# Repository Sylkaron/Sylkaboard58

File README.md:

# Sylkaboard58

A split ortholinear keyboard with 58 keys and two encoders for a first step in my ergonomic journey

## Table des matières
- [Overview](#-overview)
- [BOM](#️-bill-of-materials)
- [Assemblage](#-assemblage)
- [Firmware](#-firmware)
- [Layout](#-keyboard-layout)
- [Licence](#-licence)

## Overview

## BOM
 ### Keyboard

 ### Tools

## Firmware
Powered by QMK

### Requirements
- [QMK Toolbox](https://github.com/qmk/qmk_toolbox) (to flash firmware).
- [QMK Firmware](https://github.com/qmk/qmk_firmware)

### Étapes pour flasher le firmware
1. Téléchargez ou clonez le dépôt QMK :
   ```bash
   git clone https://github.com/qmk/qmk_firmware.git

## Layout

## Licence  
This project is under **[CERN OHL v2](https://ohwr.org/cern_ohl)** 
This documentation is under **[CC BY-SA 4.0](https://creativecommons.org/licenses/by-sa/4.0/)**.

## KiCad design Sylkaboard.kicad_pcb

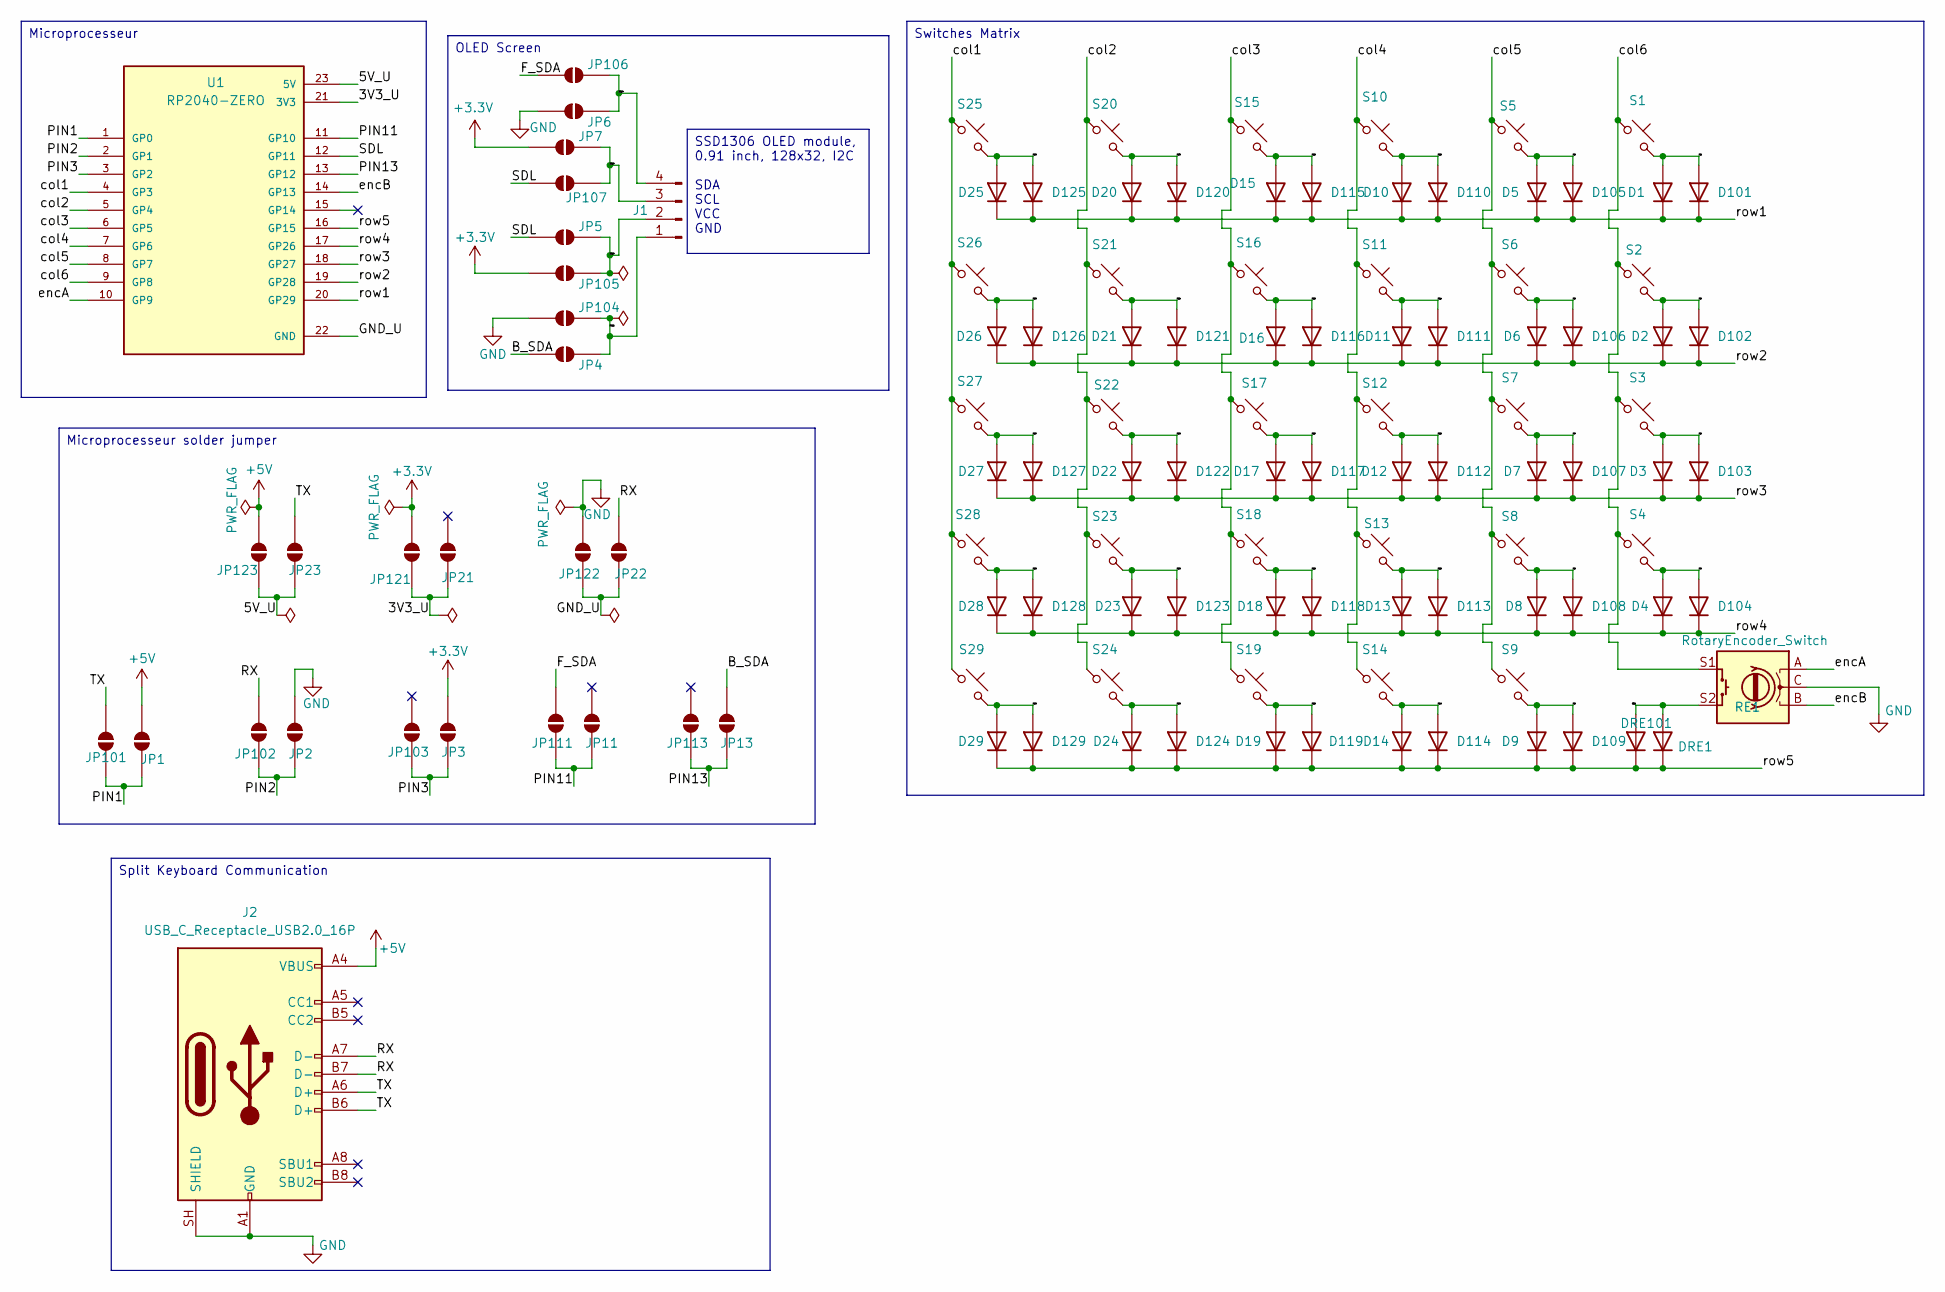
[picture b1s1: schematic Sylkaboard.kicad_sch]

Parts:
D1, D2, D3, D4, D5, D6, D7, D8, D9, D10, D11, D12, D13, D14, D15, D16, D17, D18, D19, D20, D21, D22, D23, D24, D25, D26, D27, D28, D29, D101, D102, D103, D104, D105, D106, D107, D108, D109, D110, D111, D112, D113, D114, D115, D116, D117, D118, D119, D120, D121, D122, D123, D124, D125, D126, D127, D128, D129: 1N4148W; D_SOD-123
DRE1, DRE101: 1N4148W; D_SOD-123
J1: Conn_01x04_Pin; PinHeader_1x04_P2.54mm_Vertical
J2: USB_C_Receptacle_USB2.0_16P; USB_C_Receptacle_G-Switch_GT-USB-7010ASV_REVERSIBLE
JP1, JP2, JP3, JP4, JP5, JP6, JP7, JP11, JP13, JP21, JP22, JP23, JP101, JP102, JP103, JP104, JP105, JP106, JP107, JP111, JP113, JP121, JP122, JP123: SolderJumper_2_Open; SolderJumper-2_P1.3mm_Open_TrianglePad1.0x1.5mm
RE1: RotaryEncoder_Switch; RotaryEncoder_Alps_EC11E-Switch_Vertical_H20mm
S1, S2, S3, S4, S5, S6, S7, S8, S9, S10, S11, S12, S13, S14, S15, S16, S17, S18, S19, S20, S21, S22, S23, S24, S25, S26, S27, S28, S29: SW_Push_45deg; Kail_Hotswap_Reversible_V1V2
U1: RP2040-ZERO; MODULE_RP2040-ZERO; PARTREV NA

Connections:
+3.3V: JP3.2 (B), JP7.2 (B), JP105.2 (B), JP121.2 (B)
+5V: J2.A4 (VBUS), J2.A9 (VBUS), J2.B4 (VBUS), J2.B9 (VBUS), JP1.2 (B), JP123.2 (B)
/3V3_U: JP21.1 (A_1), JP121.1 (A), U1.21 (3V3)
/5V_U: JP23.1 (A), JP123.1 (A), U1.23 (5V)
/B_SDA: JP4.2 (B), JP13.2 (B)
/F_SDA: JP106.2 (B), JP111.2 (B)
/GND_U: JP22.1 (A), JP122.1 (A), U1.22 (GND)
/OLED1: J1.1, JP4.1 (A), JP104.1 (A)
/OLED2: J1.2, JP5.1 (A), JP105.1 (A)
/OLED3: J1.3, JP7.1 (A), JP107.1 (A)
/OLED4: J1.4, JP6.1 (A), JP106.1 (A)
/PIN1: JP1.1 (A), JP101.1 (A), U1.1 (GP0)
/PIN2: JP2.1 (A), JP102.1 (A), U1.2 (GP1)
/PIN3: JP3.1 (A), JP103.1 (A_1), U1.3 (GP2)
/PIN11: JP11.1 (A_1), JP111.1 (A), U1.11 (GP10)
/PIN13: JP13.1 (A), JP113.1 (A_1), U1.13 (GP12)
/RED1: DRE1.2 (A), DRE101.2 (A), RE1.S2
/RX: J2.A7 (D-), J2.B7 (D-), JP22.2 (B), JP102.2 (B)
/SD1: D1.2 (A), D101.2 (A), S1.2
/SD2: D2.2 (A), D102.2 (A), S2.2
/SD3: D3.2 (A), D103.2 (A), S3.2
/SD4: D4.2 (A), D104.2 (A), S4.2
/SD5: D5.2 (A), D105.2 (A), S5.2
/SD6: D6.2 (A), D106.2 (A), S6.2
/SD7: D7.2 (A), D107.2 (A), S7.2
/SD8: D8.2 (A), D108.2 (A), S8.2
/SD9: D9.2 (A), D109.2 (A), S9.2
/SD10: D10.2 (A), D110.2 (A), S10.2
/SD11: D11.2 (A), D111.2 (A), S11.2
/SD12: D12.2 (A), D112.2 (A), S12.2
/SD13: D13.2 (A), D113.2 (A), S13.2
/SD14: D14.2 (A), D114.2 (A), S14.2
/SD15: D15.2 (A), D115.2 (A), S15.2
/SD16: D16.2 (A), D116.2 (A), S16.2
/SD17: D17.2 (A), D117.2 (A), S17.2
/SD18: D18.2 (A), D118.2 (A), S18.2
/SD19: D19.2 (A), D119.2 (A), S19.2
/SD20: D20.2 (A), D120.2 (A), S20.2
/SD21: D21.2 (A), D121.2 (A), S21.2
/SD22: D22.2 (A), D122.2 (A), S22.2
/SD23: D23.2 (A), D123.2 (A), S23.2
/SD24: D24.2 (A), D124.2 (A), S24.2
/SD25: D25.2 (A), D125.2 (A), S25.2
/SD26: D26.2 (A), D126.2 (A), S26.2
/SD27: D27.2 (A), D127.2 (A), S27.2
/SD28: D28.2 (A), D128.2 (A), S28.2
/SD29: D29.2 (A), D129.2 (A), S29.2
/SDL: JP5.2 (B), JP107.2 (B), U1.12 (GP11)
/TX: J2.A6 (D+), J2.B6 (D+), JP23.2 (B), JP101.2 (B)
/col1: S25.1, S26.1, S27.1, S28.1, S29.1, U1.4 (GP3)
/col2: S20.1, S21.1, S22.1, S23.1, S24.1, U1.5 (GP4)
/col3: S15.1, S16.1, S17.1, S18.1, S19.1, U1.6 (GP5)
/col4: S10.1, S11.1, S12.1, S13.1, S14.1, U1.7 (GP6)
/col5: S5.1, S6.1, S7.1, S8.1, S9.1, U1.8 (GP7)
/col6: RE1.S1, S1.1, S2.1, S3.1, S4.1, U1.9 (GP8)
/encA: RE1.A, U1.10 (GP9)
/encB: RE1.B, U1.14 (GP13)
/row1: D1.1 (K), D5.1 (K), D10.1 (K), D15.1 (K), D20.1 (K), D25.1 (K), D101.1 (K), D105.1 (K), D110.1 (K), D115.1 (K), D120.1 (K), D125.1 (K), U1.20 (GP29)
/row2: D2.1 (K), D6.1 (K), D11.1 (K), D16.1 (K), D21.1 (K), D26.1 (K), D102.1 (K), D106.1 (K), D111.1 (K), D116.1 (K), D121.1 (K), D126.1 (K), U1.19 (GP28)
/row3: D3.1 (K), D7.1 (K), D12.1 (K), D17.1 (K), D22.1 (K), D27.1 (K), D103.1 (K), D107.1 (K), D112.1 (K), D117.1 (K), D122.1 (K), D127.1 (K), U1.18 (GP27)
/row4: D4.1 (K), D8.1 (K), D13.1 (K), D18.1 (K), D23.1 (K), D28.1 (K), D104.1 (K), D108.1 (K), D113.1 (K), D118.1 (K), D123.1 (K), D128.1 (K), U1.17 (GP26)
/row5: D9.1 (K), D14.1 (K), D19.1 (K), D24.1 (K), D29.1 (K), D109.1 (K), D114.1 (K), D119.1 (K), D124.1 (K), D129.1 (K), DRE1.1 (K), DRE101.1 (K), U1.16 (GP15)
GND: J2.A1 (GND), J2.A12 (GND), J2.B1 (GND), J2.B12 (GND), J2.SH (SHIELD), JP2.2 (B), JP6.2 (B), JP104.2 (B), JP122.2 (B), RE1.C

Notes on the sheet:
Split Keyboard Communication
Microprocesseur solder jumper
Microprocesseur
SSD1306 OLED module, 0.91 inch, 128x32, I2C SDA SCL VCC GND
OLED Screen
Switches Matrix

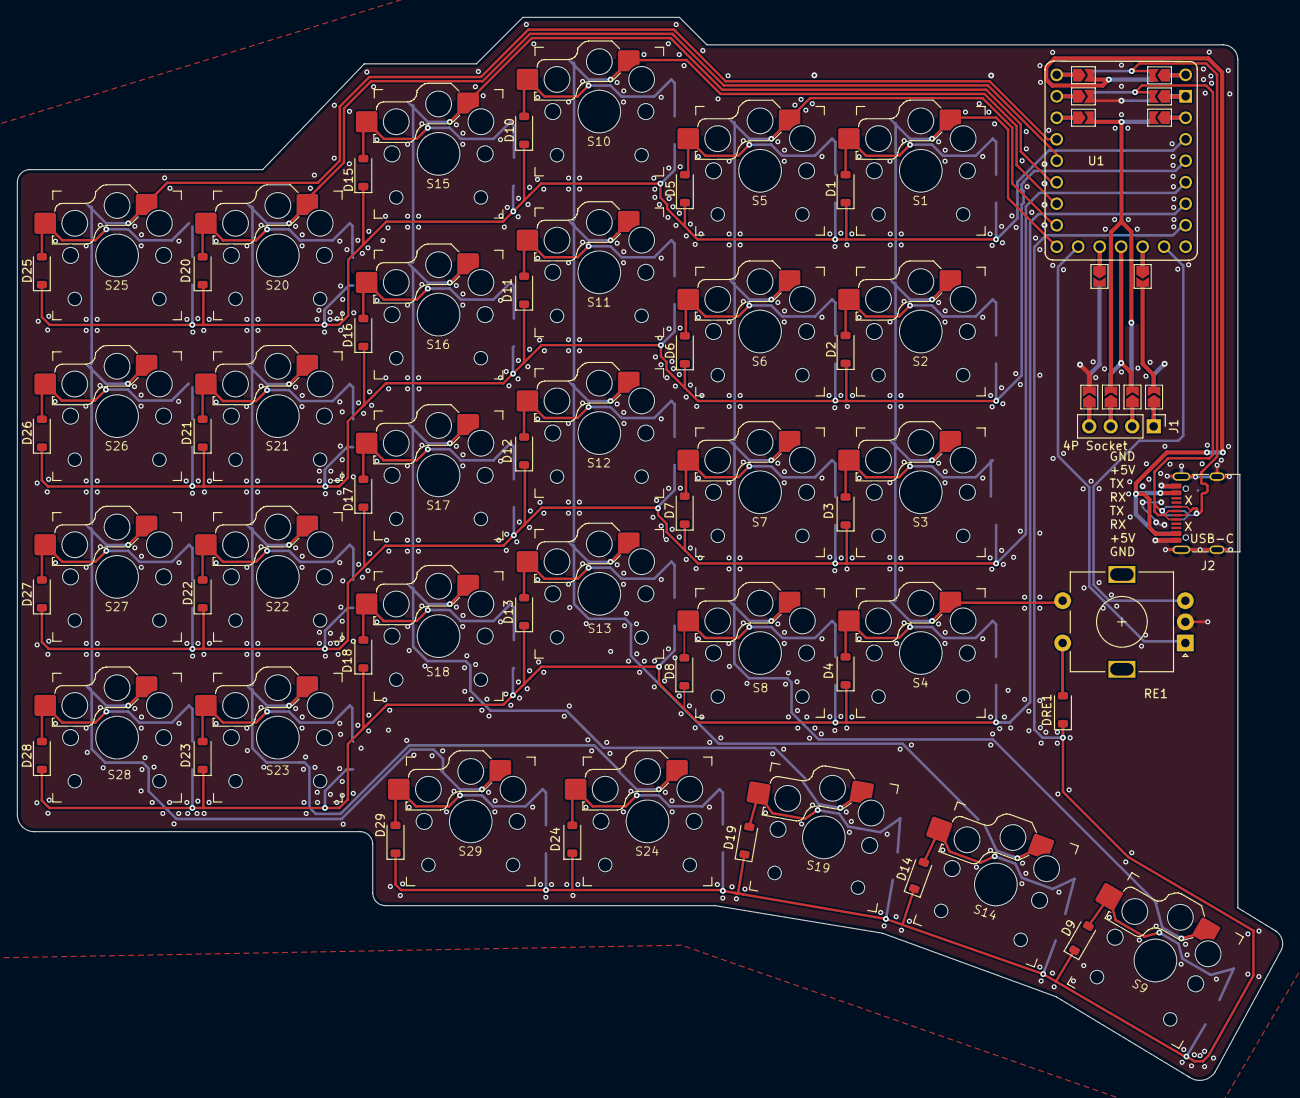
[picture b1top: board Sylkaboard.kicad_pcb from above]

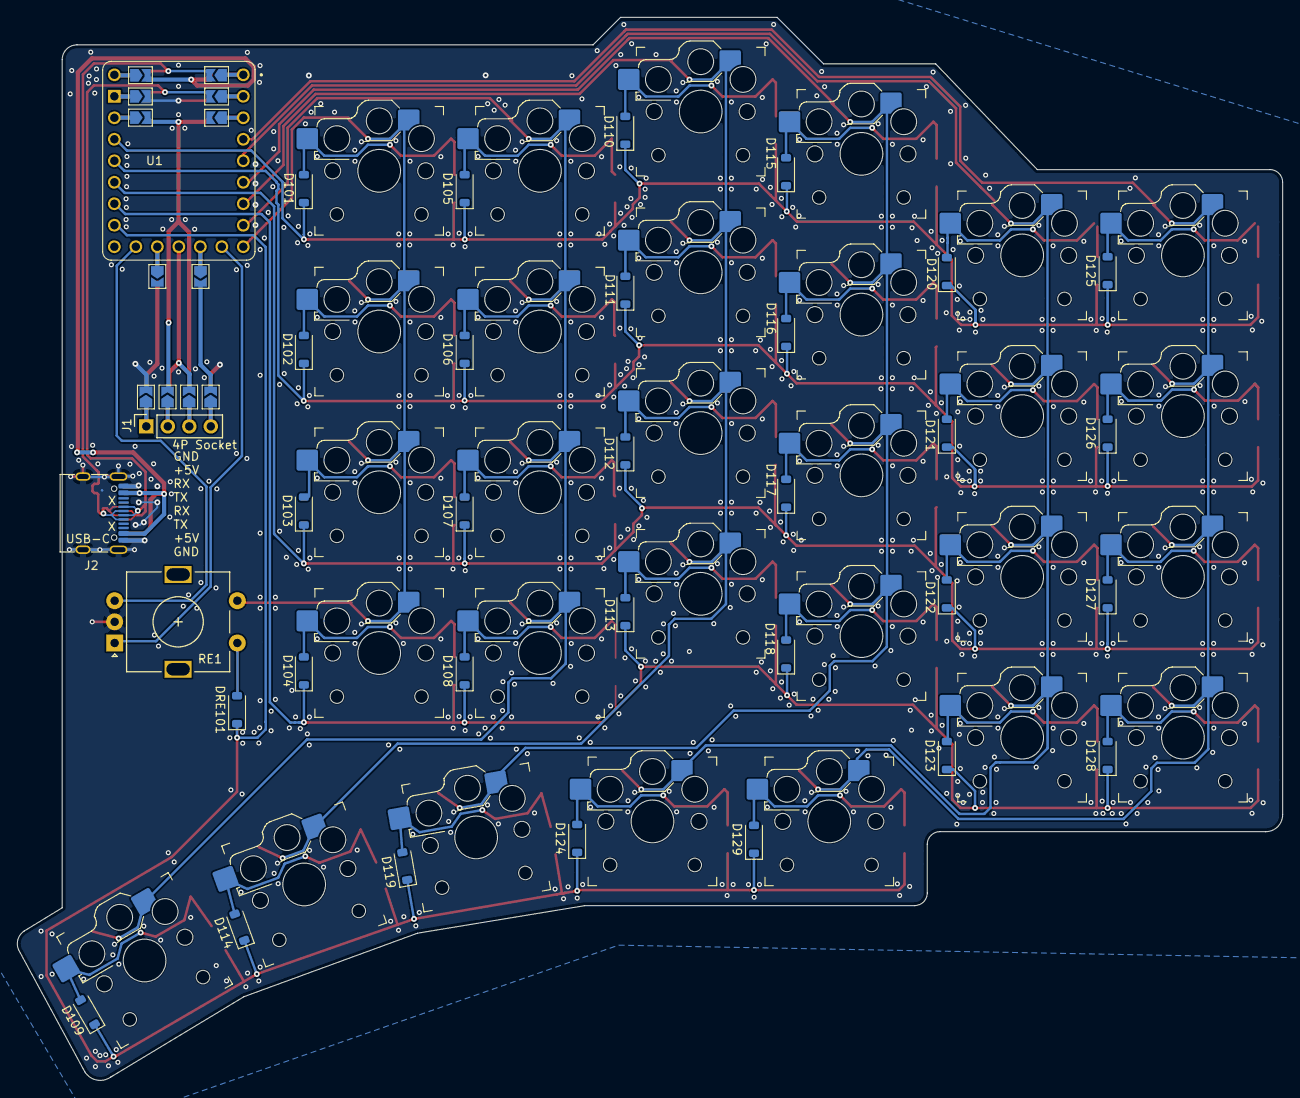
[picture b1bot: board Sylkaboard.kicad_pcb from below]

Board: 2 copper layers, 149.6 x 125.6 mm, 117 parts (43 on the bottom side), 63 nets.

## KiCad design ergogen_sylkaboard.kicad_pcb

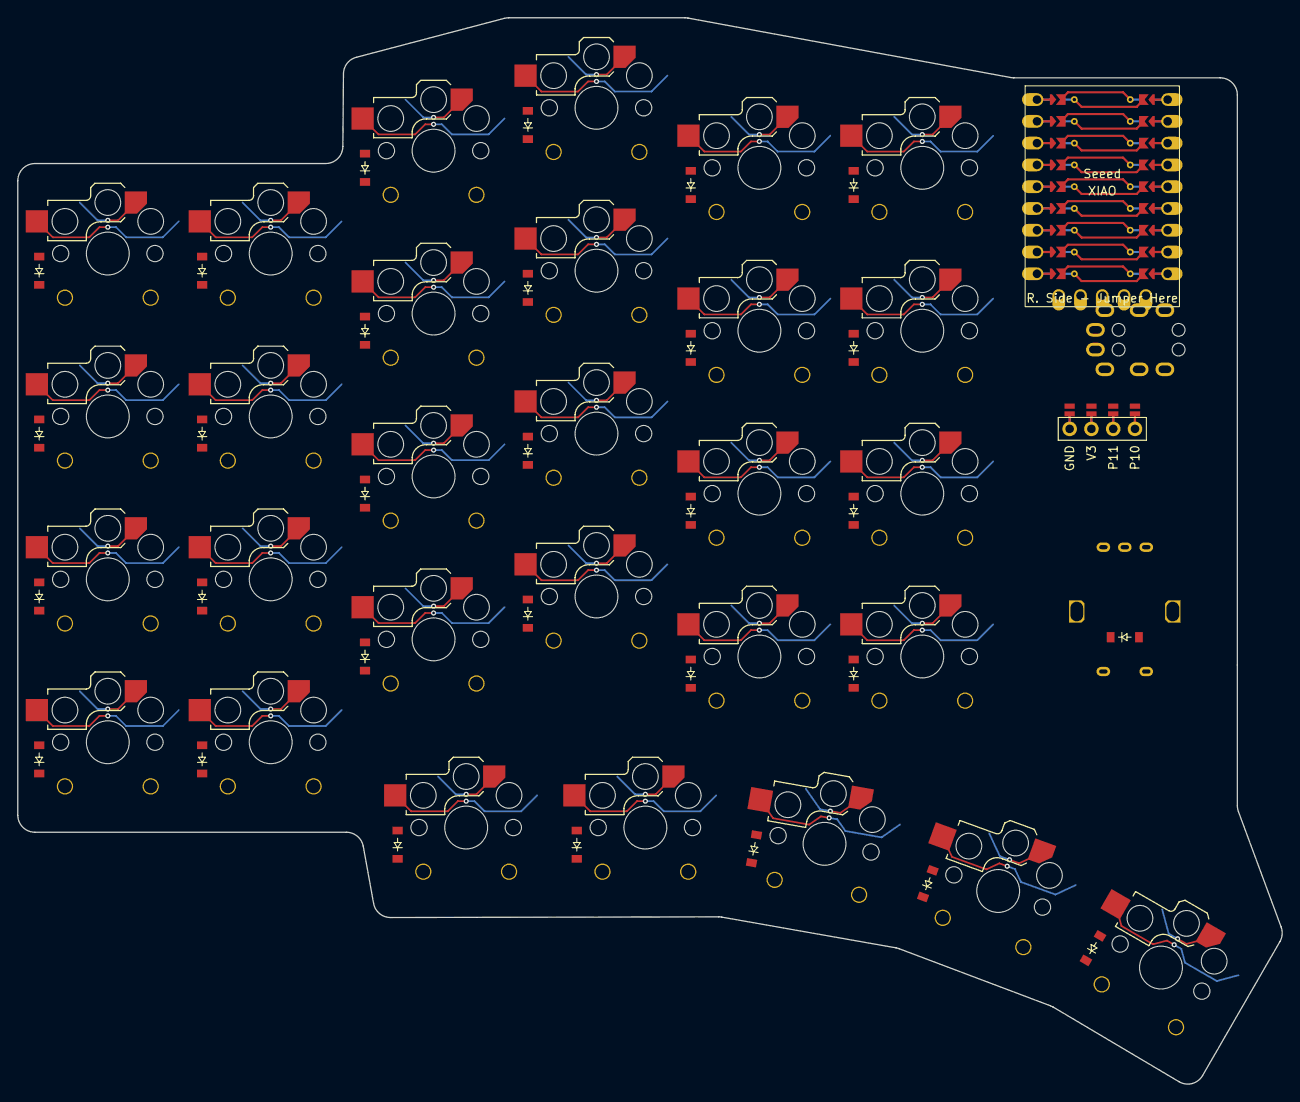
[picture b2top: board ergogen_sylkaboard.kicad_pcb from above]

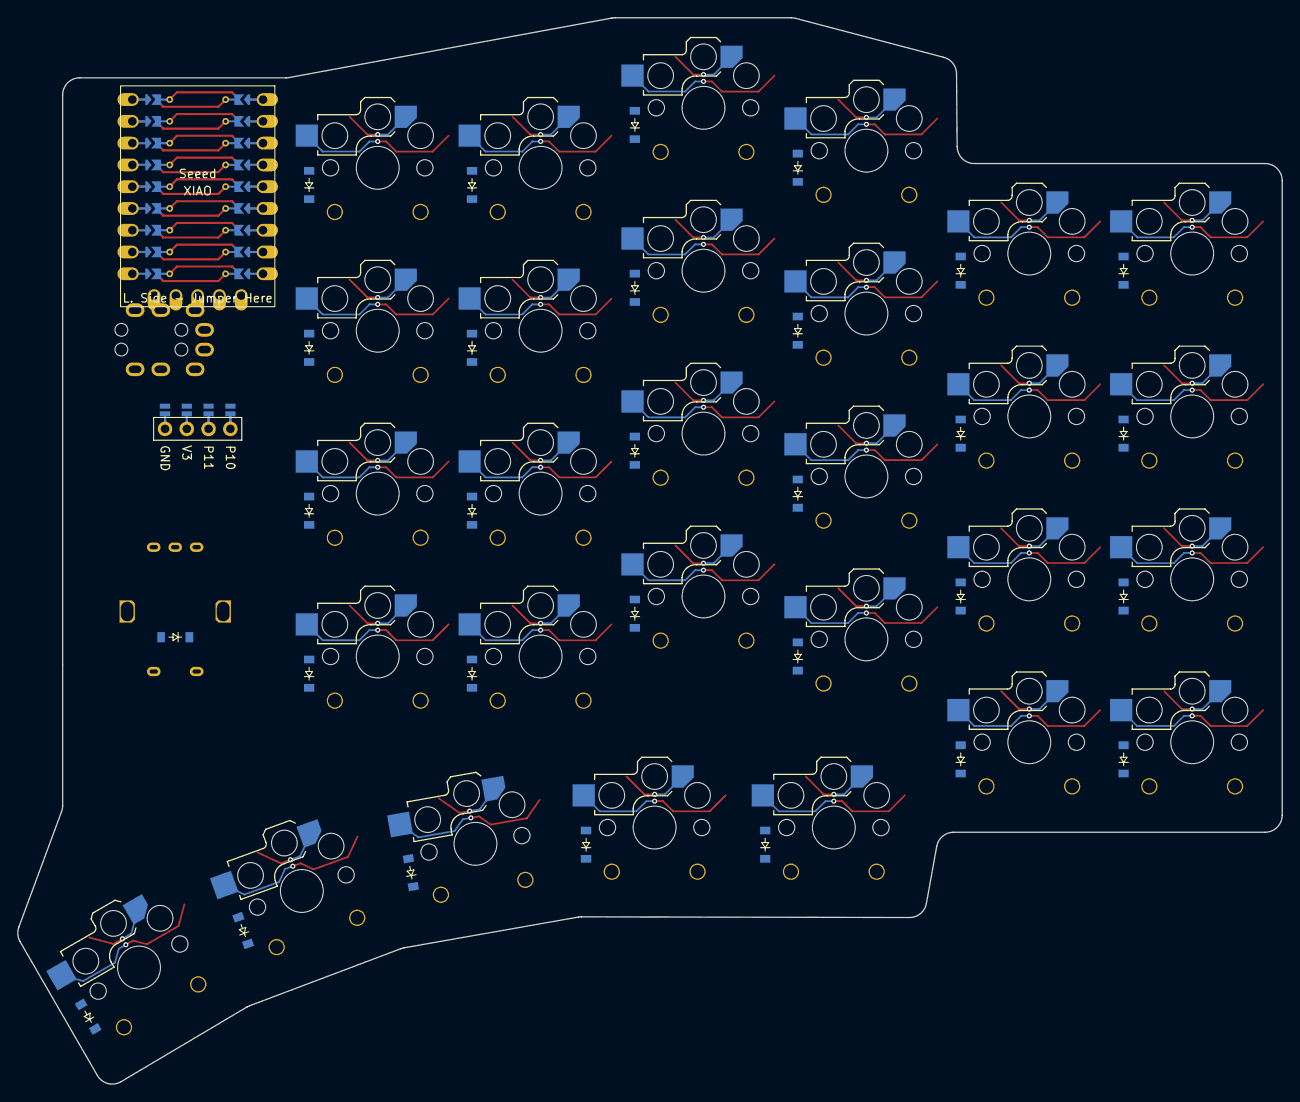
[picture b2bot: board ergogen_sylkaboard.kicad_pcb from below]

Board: 2 copper layers, 147.5 x 124.4 mm, 92 parts (59 on the bottom side), 49 nets.

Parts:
D1, D2, D3, D4, D5, D6, D7, D8, D9, D10, D11, D12, D13, D14, D15, D16, D17, D18, D19, D20, D21, D22, D23, D24, D25, D26, D27, D28, D29, D30, D31, D32, D33, D34, D35, D36, D37, D38, D39, D40, D41, D42, D43, D44, D45, D46, D47, D48, D49, D50, D51, D52, D53, D54, D55, D56, D57, D58, D59, D60: diode_tht_sod123
DISP1: display_ssd1306
RE1: rotary_encoder_ec11_ec12
S1, S2, S3, S4, S5, S6, S7, S8, S9, S10, S11, S12, S13, S14, S15, S16, S17, S18, S19, S20, S21, S22, S23, S24, S25, S26, S27, S28, S29: switch_choc_v1_v2
TRRS1: trrs_pj320a (reversible)

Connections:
DISP1_1: DISP1.1, DISP1.10, DISP1.23
DISP1_2: DISP1.2, DISP1.11, DISP1.22
DISP1_3: DISP1.3, DISP1.12, DISP1.21
DISP1_4: DISP1.4, DISP1.13, DISP1.20
GND: DISP1.14, DISP1.24, TRRS1.2
P3: D4.1, D8.1, D12.1, D16.1, D20.1, D24.1, D33.1, D37.1, D41.1, D45.1, D49.1, D53.1
P4: D3.1, D7.1, D11.1, D15.1, D19.1, D23.1, D32.1, D36.1, D40.1, D44.1, D48.1, D52.1
P5: D2.1, D6.1, D10.1, D14.1, D18.1, D22.1, D31.1, D35.1, D39.1, D43.1, D47.1, D51.1
P6: D1.1, D5.1, D9.1, D13.1, D17.1, D21.1, D30.1, D34.1, D38.1, D42.1, D46.1, D50.1
P7: D25.1, D26.1, D27.1, D28.1, D29.1, D54.1, D55.1, D56.1, D57.1, D58.1, D59.1, D60.1
P10: DISP1.17, DISP1.27, TRRS1.5
P11: DISP1.16, DISP1.26, TRRS1.3
P14: RE1.S2, S21.1, S22.1, S23.1, S24.1
P15: S17.1, S18.1, S19.1, S20.1, S29.1
P26: S13.1, S14.1, S15.1, S16.1, S28.1
P27: S9.1, S10.1, S11.1, S12.1, S27.1
P28: S5.1, S6.1, S7.1, S8.1, S26.1
P29: S1.1, S2.1, S3.1, S4.1, S25.1
V3: DISP1.15, DISP1.25
default_default: D59.2, D60.2, RE1.S1
extra_cluster: D29.2, D58.2, S29.2
gui_cluster: D25.2, D54.2, S25.2
index_bottom: D17.2, D46.2, S17.2
index_home: D18.2, D47.2, S18.2
index_num: D20.2, D49.2, S20.2
index_top: D19.2, D48.2, S19.2
inner_bottom: D21.2, D50.2, S21.2
inner_home: D22.2, D51.2, S22.2
inner_num: D24.2, D53.2, S24.2
inner_top: D23.2, D52.2, S23.2
layer_cluster: D27.2, D56.2, S27.2
middle_bottom: D13.2, D42.2, S13.2
middle_home: D14.2, D43.2, S14.2
middle_num: D16.2, D45.2, S16.2
middle_top: D15.2, D44.2, S15.2
outer_bottom: D1.2, D30.2, S1.2
outer_home: D2.2, D31.2, S2.2
outer_num: D4.2, D33.2, S4.2
outer_top: D3.2, D32.2, S3.2
pinky_bottom: D5.2, D34.2, S5.2
pinky_home: D6.2, D35.2, S6.2
pinky_num: D8.2, D37.2, S8.2
pinky_top: D7.2, D36.2, S7.2
ring_bottom: D9.2, D38.2, S9.2
ring_home: D10.2, D39.2, S10.2
ring_num: D12.2, D41.2, S12.2
ring_top: D11.2, D40.2, S11.2
space_cluster: D28.2, D57.2, S28.2
symbol_cluster: D26.2, D55.2, S26.2

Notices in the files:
README.md:
License: CERN OHL v2
